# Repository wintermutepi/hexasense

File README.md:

HexaSense
=========

This is a prototyping project for a room heating controller based on the
HexaBus architecture. Nothing spectacular to see here - this is just a
playground.

### License

The UART code is written by Peter Fleury. Everything else: BSD 2-clause
license as below:

Copyright (c) 2012, Mathias Dalheimer
All rights reserved.

Redistribution and use in source and binary forms, with or without
modification, are permitted provided that the following conditions are
met:

* Redistributions of source code must retain the above copyright notice, 
this list of conditions and the following disclaimer.

* Redistributions in binary form must reproduce the above copyright
notice, this list of conditions and the following disclaimer in the
documentation and/or other materials provided with the distribution.

THIS SOFTWARE IS PROVIDED BY THE COPYRIGHT HOLDERS AND CONTRIBUTORS "AS
IS" AND ANY EXPRESS OR IMPLIED WARRANTIES, INCLUDING, BUT NOT LIMITED
TO, THE IMPLIED WARRANTIES OF MERCHANTABILITY AND FITNESS FOR A
PARTICULAR PURPOSE ARE DISCLAIMED. IN NO EVENT SHALL THE COPYRIGHT
HOLDER OR CONTRIBUTORS BE LIABLE FOR ANY DIRECT, INDIRECT, INCIDENTAL,
SPECIAL, EXEMPLARY, OR CONSEQUENTIAL DAMAGES (INCLUDING, BUT NOT
LIMITED TO, PROCUREMENT OF SUBSTITUTE GOODS OR SERVICES; LOSS
OF USE, DATA, OR PROFITS; OR BUSINESS INTERRUPTION) HOWEVER
CAUSED AND ON ANY THEORY OF LIABILITY, WHETHER IN CONTRACT,
STRICT LIABILITY, OR TORT (INCLUDING NEGLIGENCE OR OTHERWISE)
ARISING IN ANY WAY OUT OF THE USE OF THIS SOFTWARE, EVEN IF ADVISED OF
THE POSSIBILITY OF SUCH DAMAGE.

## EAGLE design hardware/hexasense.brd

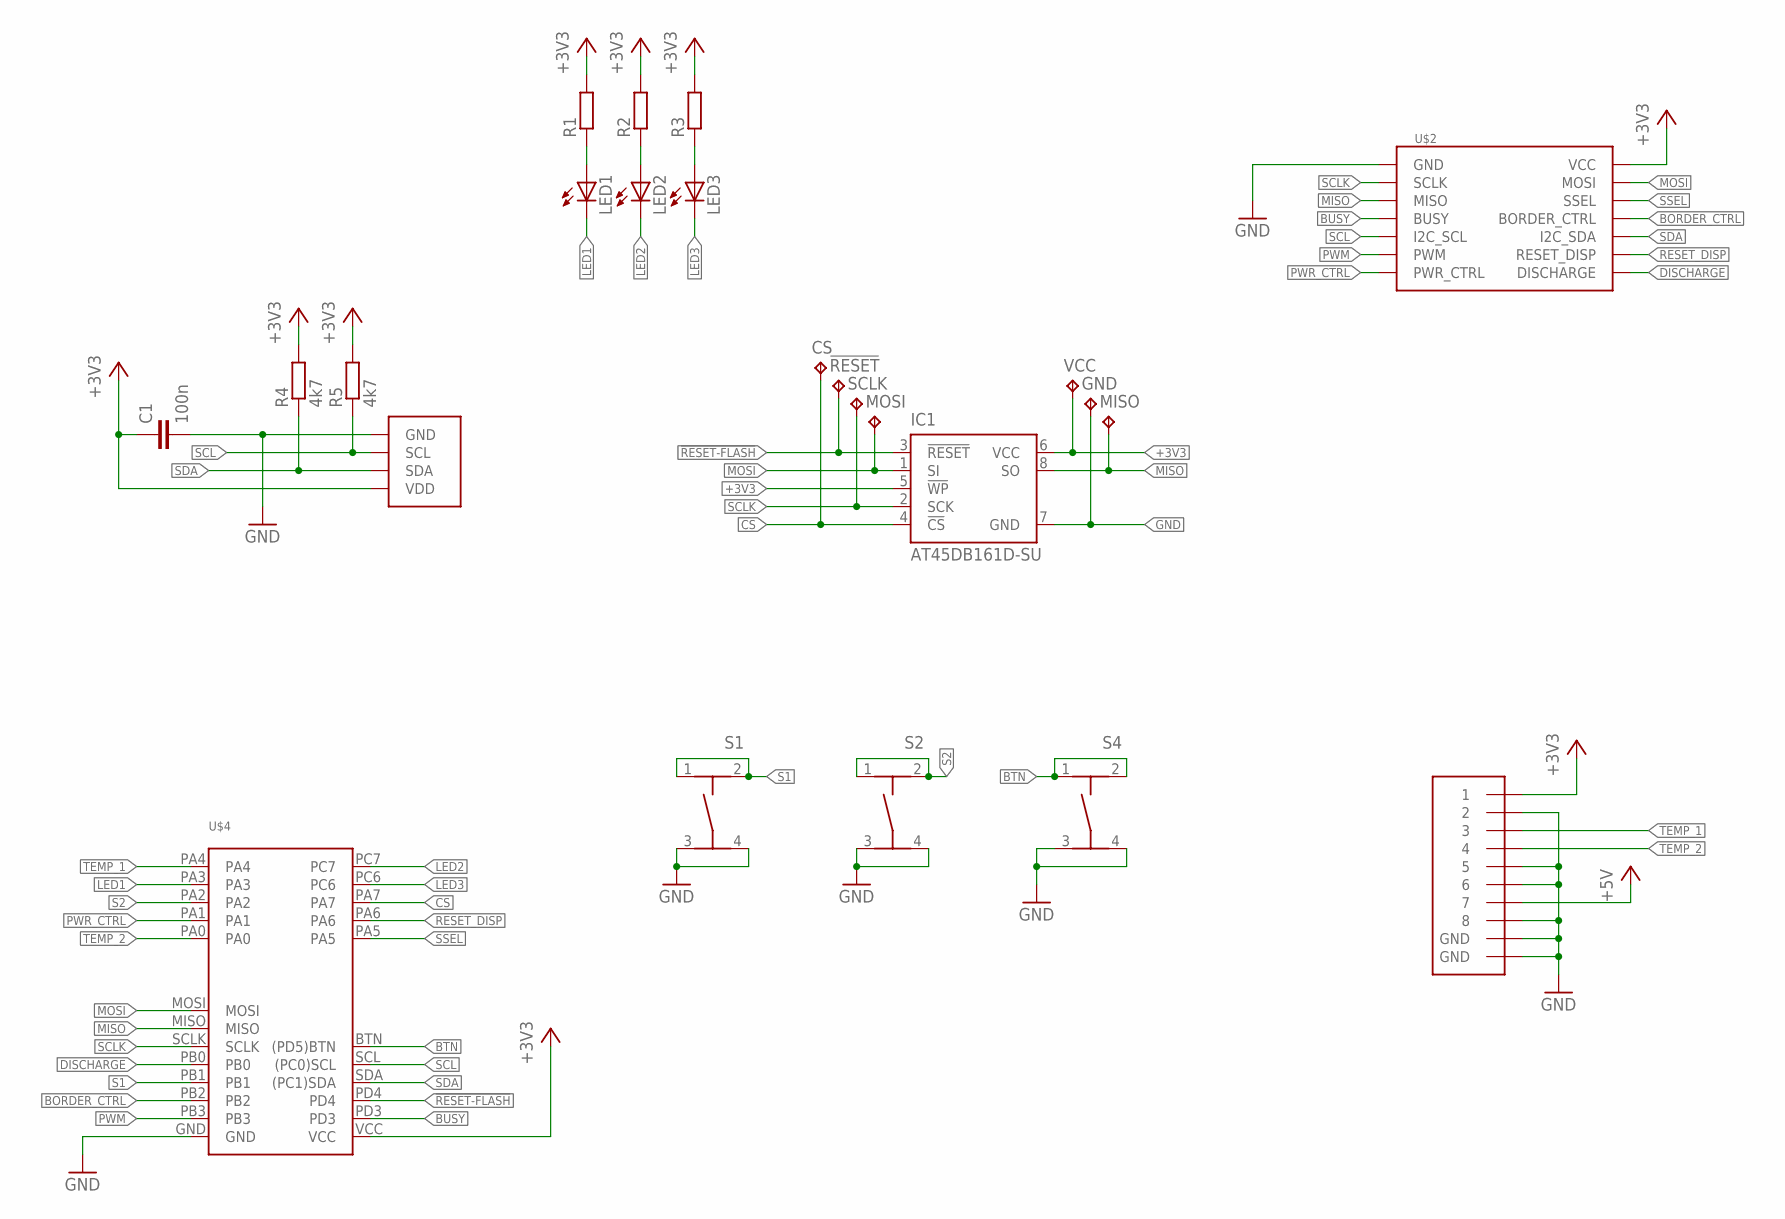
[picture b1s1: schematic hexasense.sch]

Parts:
!RESET: TPB1,27; B1,27
C1: 100n; C0805
CS: TPB1,27; B1,27
GND: TPB1,27; B1,27
IC1: AT45DB161D-SU; 8S2
LED1, LED2, LED3: LED3MM
MISO: TPB1,27; B1,27
MOSI: TPB1,27; B1,27
R1, R2, R3: R-EU_R0805; R0805
R4, R5: 4k7; R0805
S1, S2, S4: TASTER-9314_SMD
SCLK: TPB1,27; B1,27
U$1: MEBP8-8G; RJ45-REICHELT
U$2: EPAPER
U$4: HEXABUS
U$7: HYT271
VCC: TPB1,27; B1,27

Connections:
!RESET-FLASH: !RESET.TP, IC1.3 (!RESET), U$4.PD4
+3V3: C1.1, IC1.5 (!WP), IC1.6 (VCC), R1.2, R2.2, R3.2, R4.2, R5.2, U$1.1, U$2.P2 (VCC), U$4.VCC, U$7.VDD, VCC.TP
+5V: U$1.7
BORDER_CTRL: U$2.P8 (BORDER_CTRL), U$4.PB2
BTN: S4.1, S4.2, U$4.BTN ((PD5)BTN)
BUSY: U$2.P7 (BUSY), U$4.PD3
CS: CS.TP, IC1.4 (!CS), U$4.PA7
DISCHARGE: U$2.P14 (DISCHARGE), U$4.PB0
GND: C1.2, GND.TP, IC1.7 (GND), S1.3, S1.4, S2.3, S2.4, S4.3, S4.4, U$1.2, U$1.5, U$1.6, U$1.8, U$1.GND@1 (GND), U$1.GND@2 (GND), U$2.P1 (GND), U$4.GND, U$7.GND
LED1: LED1.K (C), U$4.PA3
LED2: LED2.K (C), U$4.PC7
LED3: LED3.K (C), U$4.PC6
MISO: IC1.8 (SO), MISO.TP, U$2.P5 (MISO), U$4.MISO
MOSI: IC1.1 (SI), MOSI.TP, U$2.P4 (MOSI), U$4.MOSI
unnamed: LED3.A, R3.1
unnamed: LED2.A, R2.1
unnamed: LED1.A, R1.1
PWM: U$2.P11 (PWM), U$4.PB3
PWR_CTRL: U$2.P13 (PWR_CTRL), U$4.PA1
RESET_DISP: U$2.P12 (RESET_DISP), U$4.PA6
S1: S1.1, S1.2, U$4.PB1
S2: S2.1, S2.2, U$4.PA2
SCL: R5.1, U$2.P9 (I2C_SCL), U$4.SCL ((PC0)SCL), U$7.SCL
SCLK: IC1.2 (SCK), SCLK.TP, U$2.P3 (SCLK), U$4.SCLK
SDA: R4.1, U$2.P10 (I2C_SDA), U$4.SDA ((PC1)SDA), U$7.SDA
SSEL: U$2.P6 (SSEL), U$4.PA5
TEMP_1: U$1.3, U$4.PA4
TEMP_2: U$1.4, U$4.PA0

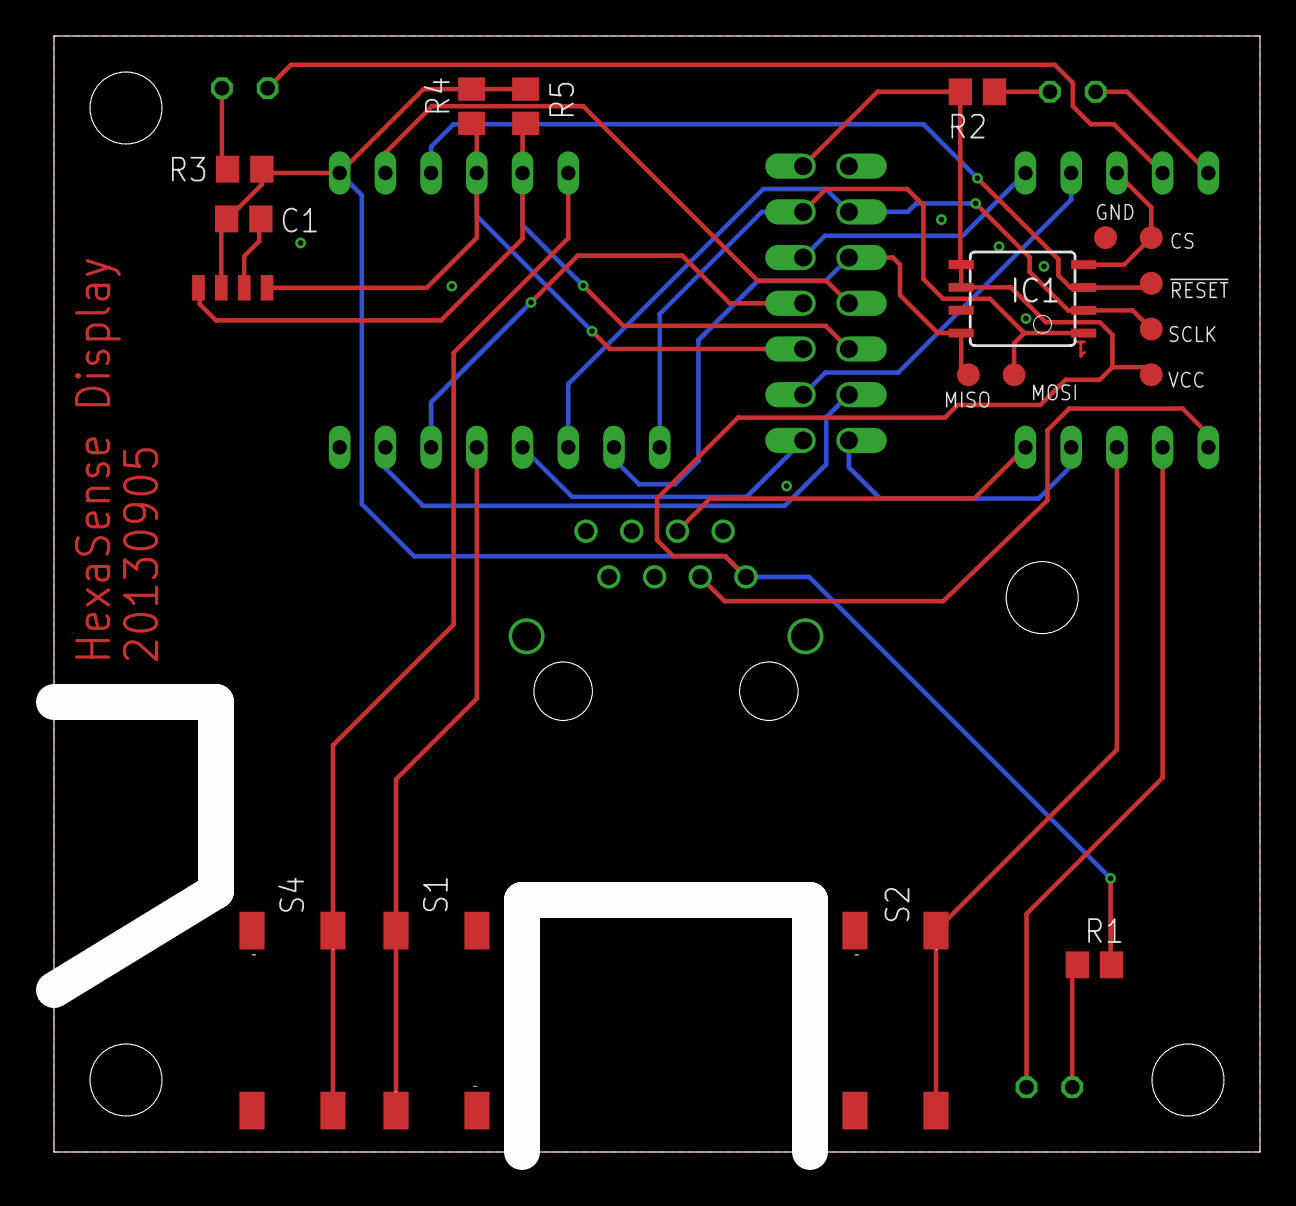
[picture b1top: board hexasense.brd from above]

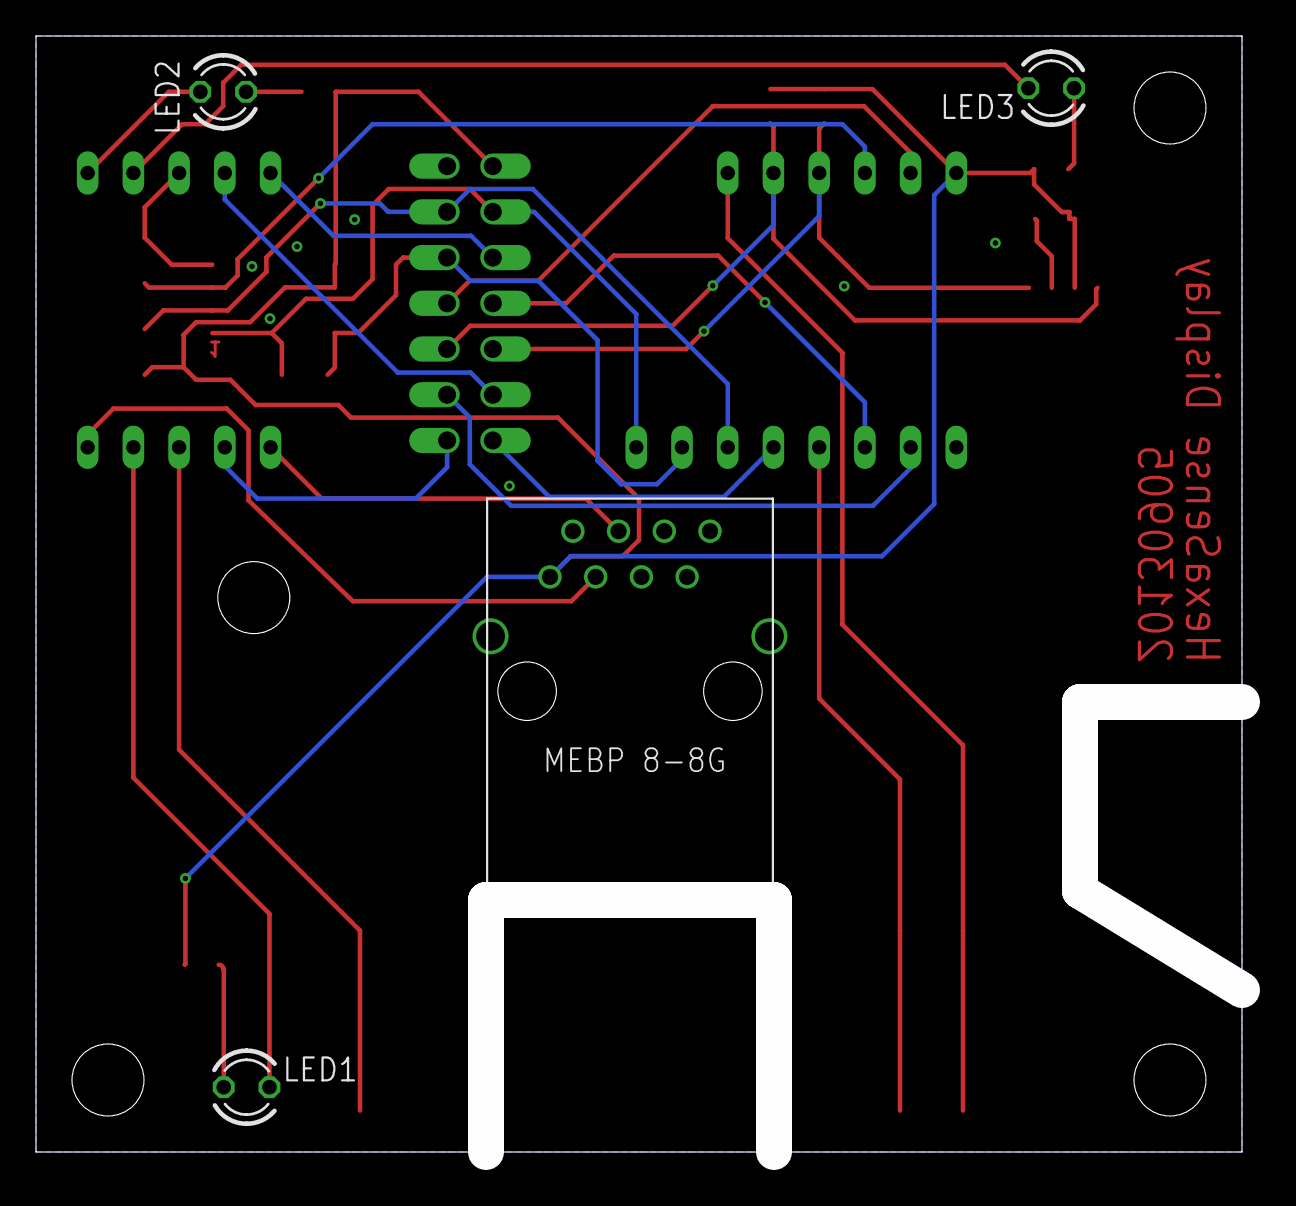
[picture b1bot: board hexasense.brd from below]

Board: 2 copper layers, 66.0 x 61.0 mm, 24 parts (5 on the bottom side), 27 nets.

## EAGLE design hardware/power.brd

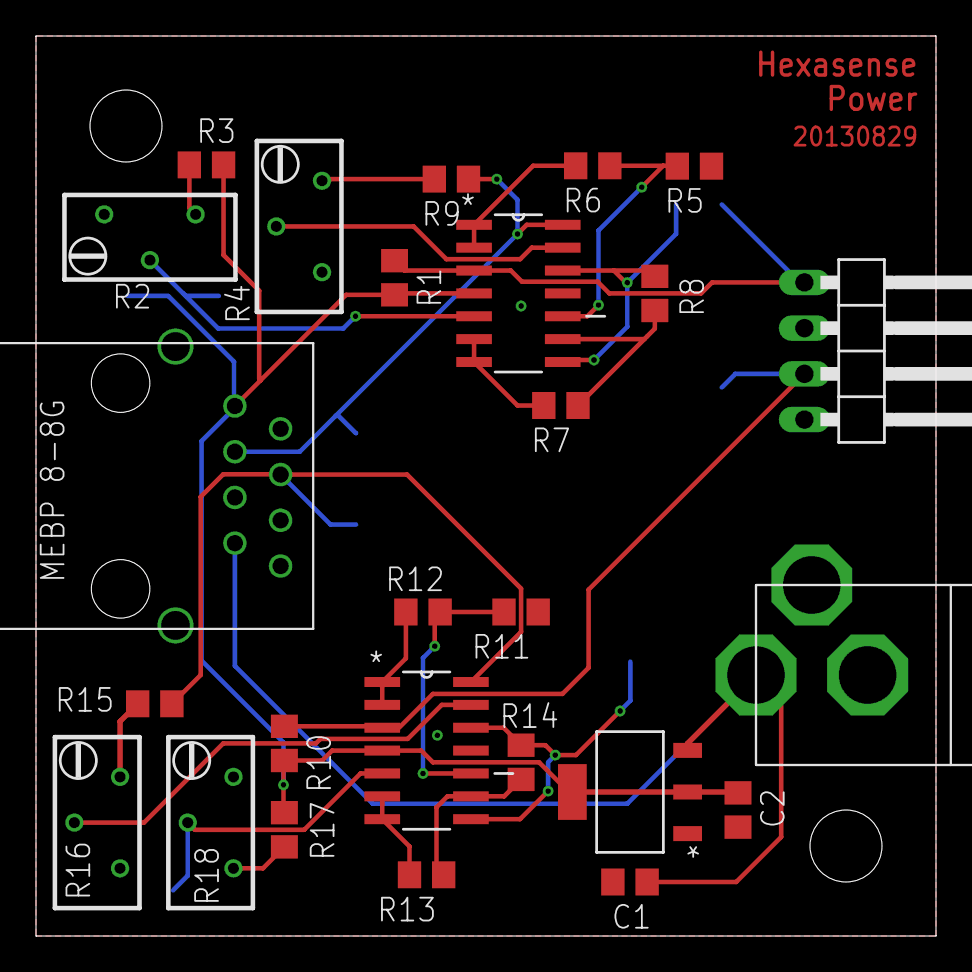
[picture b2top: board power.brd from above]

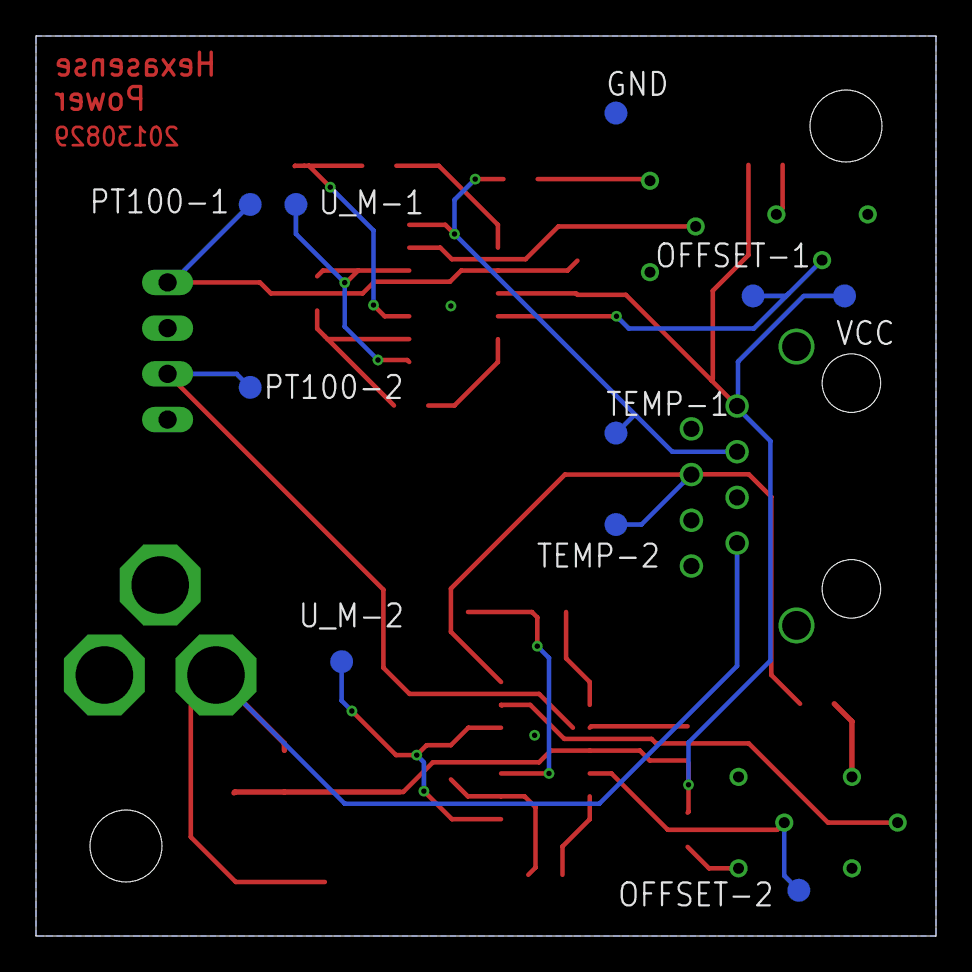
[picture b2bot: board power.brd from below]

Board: 2 copper layers, 50.0 x 50.0 mm, 36 parts (10 on the bottom side), 25 nets.

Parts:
C1, C2: 10uF; C0805
GND: TPB1,27; B1,27
JP2: 1X04/90
OFFSET-1, OFFSET-2: TPB1,27; B1,27
PT100-1, PT100-2: TPB1,27; B1,27
R1, R10: 1k; R0805
R2, R18: 10k; RTRIMT93YB
R3, R17: 100k; R0805
R4, R16: 20k; RTRIMT93YB
R5, R6, R7, R8, R11, R12, R13, R14: 470k; R0805
R9, R15: 47k; R0805
TEMP-1, TEMP-2: TPB1,27; B1,27
U1, U2: LM324D; SOIC127P600X175-14N
U3: LM1117MP-3.3; SOT230P696X180-4N
U$1: MEBP8-8G; RJ45-REICHELT
U$2: HOHLBUCHSE
U_M-1, U_M-2: TPB1,27; B1,27
VCC: TPB1,27; B1,27

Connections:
+3V3: C2.1, R1.2, R3.2, R10.2, R17.2, U1.4, U2.4, U3.2, U3.4, U$1.1, VCC.TP
+5V: C1.1, U3.3, U$1.7, U$2.I
GND: C1.2, C2.2, GND.TP, JP2.2, JP2.4, R2.3, R4.1, R5.1, R11.1, R16.1, R18.3, U1.11, U2.11, U3.1, U$1.2, U$1.5, U$1.6, U$1.8, U$1.GND@1, U$1.GND@2, U$2.O
unnamed: R4.2, U1.13
unnamed: R5.2, R6.1, U1.10
unnamed: R2.1, R3.1
unnamed: R15.2, R16.3
unnamed: R6.2, U1.1, U1.2
unnamed: R16.2, U2.13
unnamed: R7.2, U1.6, U1.7
unnamed: R7.1, R8.1, U1.9
unnamed: R11.2, R12.1, U2.10
unnamed: R12.2, U2.1, U2.2
unnamed: R4.3, R9.2
unnamed: R13.2, U2.6, U2.7
unnamed: R13.1, R14.1, U2.9
unnamed: R17.1, R18.1
OFFSET_1: OFFSET-1.TP, R2.2, U1.5
OFFSET_2: OFFSET-2.TP, R18.2, U2.5
PT100_1: JP2.1, PT100-1.TP, R1.1, U1.3
PT100_2: JP2.3, PT100-2.TP, R10.1, U2.3
TEMP_1: R9.1, TEMP-1.TP, U1.14, U$1.3
TEMP_2: R15.1, TEMP-2.TP, U2.14, U$1.4
U_M_1: R8.2, U1.8, U1.12, U_M-1.TP
U_M_2: R14.2, U2.8, U2.12, U_M-2.TP

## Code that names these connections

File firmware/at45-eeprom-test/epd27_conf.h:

#ifndef EPD27_CONF_H
#define EPD27_CONF_H 1

/**
 * Definition for the 2"7 display
 */

// output
#define EPD_PIN_EPD_CS PA5
#define EPD_PORT_EPD_CS PORTA
#define EPD_DDR_EPD_CS DDRA

// output
#define EPD_PIN_PANEL_ON PA1
#define EPD_PORT_PANEL_ON PORTA
#define EPD_DDR_PANEL_ON DDRA

// BORDER 
#define EPD_PIN_BORDER PB2
#define EPD_PORT_BORDER PORTB
#define EPD_DDR_BORDER DDRB

// output
#define EPD_PIN_DISCHARGE PB0
#define EPD_PORT_DISCHARGE PORTB
#define EPD_DDR_DISCHARGE DDRB

// output
#define EPD_PIN_PWM PB3
#define EPD_PORT_PWM PORTB
#define EPD_DDR_PWM DDRB

// output
#define EPD_PIN_RESET PA6
#define EPD_PORT_RESET PORTA
#define EPD_DDR_RESET DDRA

//input
#define EPD_PIN_BUSY PD3
#define EPD_PORT_BUSY PORTD
#define EPD_INPUT_PORT_BUSY PIND
#define EPD_DDR_BUSY DDRD

#define STAGE_TIME 630
#define LINES_PER_DISPLAY 176
#define DOTS_PER_LINE 264
#define BYTES_PER_LINE 264/8
#define BYTES_PER_SCAN 176/4
#define FILLER true



#endif /* EPD27_CONF_H */

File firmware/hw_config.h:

#ifndef HW_CONFIG_H
#define HW_CONFIG_H 1

/**
 * Connection of the DHT22 sensor.
 */
#define DHT22_PIN    PD3
#define DHT22_PORT   PORTD
#define DHT22_DDR    DDRD
#define DHT22_PINC   PIND


/**
 * Connection of the first button: PA1
 */
#define BTN0_DDR	DDRA
#define BTN0_PORT	PORTA
#define BTN0_PIN	PA1
#define BTN0_IN		PINA

/**
 * Connection of the second button: PA2
 */
#define BTN1_DDR	DDRA
#define BTN1_PORT	PORTA
#define BTN1_PIN	PA2
#define BTN1_IN		PINA

/**
 * Connection of the third button: PA3
 */
#define BTN2_DDR	DDRA
#define BTN2_PORT	PORTA
#define BTN2_PIN	PA3
#define BTN2_IN		PINA






#endif /* HW_CONFIG_H */

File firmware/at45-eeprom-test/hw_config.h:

#ifndef HW_CONFIG_H
#define HW_CONFIG_H 1

/**
<<<<<<< HEAD
 * Connection of the first button: PA1
=======
 * Connection of the first button
>>>>>>> dk-bringup
 */
#define BTN0_DDR	DDRB
#define BTN0_PORT	PORTB
#define BTN0_PIN	PB1
#define BTN0_IN		PINB

/**
<<<<<<< HEAD
 * Connection of the second button: PA2
=======
 * Connection of the second button
>>>>>>> dk-bringup
 */
#define BTN1_DDR	DDRA
#define BTN1_PORT	PORTA
#define BTN1_PIN	PA2
#define BTN1_IN		PINA

/**
<<<<<<< HEAD
=======
 * Connection of the third button (hxb-pairing button)
 */
#define BTN2_DDR	DDRD
#define BTN2_PORT	PORTD
#define BTN2_PIN	PD5
#define BTN2_IN		PIND

/**
>>>>>>> dk-bringup
 * I2C error codes.
 */
#define I2C_ERROR 1
#define I2C_SUCCESS 0

/**
 * PCA9532 I2C bus definitions
 */
#define PCA9532_ADDR  0xC0
#define PCA9532_FULL 0x55
#define PCA9532_OFF 0x00

/**
 * HYT271 I2C bus definitions
 */
#define HYT271_ADDR (0x28 << 1)
#define HYT271_CONV_DELAY 6
#define HYT271_BUFFER_LEN 4

/**
 * analog temperature sensors and respective adc channel
 */
#define ANALOG_TEMPERATURE_0 0
#define ANALOG_TEMPERATURE_1 4

#endif /* HW_CONFIG_H */

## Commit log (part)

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2012-12-18 redone humidity sensor package
2012-12-18 rearranged schematic
2012-12-18 further rearrangement of LEDs, some routing
2013-01-03 implemented button abstraction.
2013-01-03 minor updates on the comments, code cleanup
2013-01-03 added readme, formatting.
2013-01-04 added LED driver chip
2013-01-04 added push buttons and completed schematic for LED driver
2013-01-07 added led driver
2013-01-07 switched to Autodesk Inventor for enclosure design
2013-01-07 abandoning.
2013-01-07 new design, several components (used derive)
2013-01-07 might work.
2013-01-09 redesign completed (except for screw head)
2013-01-10 changed screw to self-tapping DIN 7981
2013-01-10 first release candidate
2013-01-11 added milling
2013-01-11 removed +12V from RJ45 connector
2013-01-11 new position for the push buttons. therefore a lot of rearanging
2013-01-11 minor tweaks, 3mm thickness for all walls.
2013-01-11 moved to power_board subdirectory
2013-01-11 done the routing
2013-01-11 first components of sense enclosure
2013-01-11 update of STL files.
2013-01-14 changed placement of buttons and leds. Did the necessary rerouting. Added a version number.
2013-01-14 schraubendim. korrigiert, ausschnitte vergroessert
2013-01-14 implemented a simple PCB model.
2013-01-14 added pcb model
2013-01-15 changed drill size
2013-01-15 replaced some parts. rearranged parts
2013-01-16 completed rerouting
2013-01-16 updated version number
2013-01-16 Changed outer distance to 6mm. Fixes #2
2013-01-18 added capacitor for volage regulator. Fixing #9
2013-01-18 basic outline of base component defined.
2013-01-21 fixes #13
2013-01-21 incresed drill size for humidity sensor. Fixes #11
2013-01-21 cleanup at RJ45 connector, finalized LM324
2013-01-21 duplicated measuring aplifier
2013-01-21 preliminary placement of new parts. ripup *
2013-01-22 corrected some wiring errors around the measuring amp
2013-01-22 added 2nd temperature signal to schematic
2013-01-22 basic routines are working on hardware prototype
2013-01-22 routing of 2nd temperature signal and pullups
2013-01-23 added led driver boilerplate code, adjusted hardware config accordingly.
2013-01-23 added empty routine for conversion from adc value to temperature
2013-01-23 code for temperature conversion - not yet testet; include .swp files in gitignore
2013-01-24 code for temperature conversion now compiling
2013-01-24 debug oputput
2013-01-24 cast adc value to float
2013-01-24 corrected upper limit
2013-01-24 set constants as float
2013-01-24 changed adc reference to internal 1.1V
2013-01-24 changed LED resistors to more fitting values
2013-01-28 played with i2c led driver.
2013-01-29 changed upper adc limit, since adc reference has been changed
2013-01-29 first prototype.
2013-01-29 fixed distance bug.
2013-01-29 test routine for gedoens
2013-01-30 output in one line, separated by semicolon
2013-01-30 holes for wall-mounting
2013-01-30 repositioned hexabus module. fixes #23
2013-01-30 added grills.
2013-01-30 schrauben hinzugefuegt
2013-01-31 ripup *
2013-01-31 added HYT271 humidity sensor
2013-01-31 resolved inconsistency between board and schematic
2013-01-31 horst
2013-01-31 loch fuer kabeldurchfuehrung hinzugefuegt
2013-01-31 lochdurchmesser vergroessert
2013-01-31 updated stl export files.
2013-01-31 changed VDD for LEDs to +5V
2013-01-31 changed LED from 0805 to 5mm THT
2013-02-01 changed pin assignment of RJ45 connector
2013-02-01 frontplatte for cnc lasercutting
2013-02-01 flanke pushbutton verlaengert
2013-02-01 led placement
2013-02-01 removed ground plane from half the PCB to avoid heating the sensor(s)
2013-02-01 increased size of grill rips to prevent slicing fuckups.
2013-02-04 added cleaned frontplatte
2013-02-04 distributed LEDs evenly
2013-02-04 optimized position of reset button
2013-02-04 cleaned up position of led resistors and started routing
2013-02-04 some of the sensors were on the wrong side of the PCB
2013-02-04 abstraktion des i2c-busses, gruppierung der leds noch unklar (see issue #27)
2013-02-04 testprogramm vollstaendig, closes #19
2013-02-05 routing...
2013-02-05 more routing...
2013-02-05 finished routing
2013-02-05 passing the DRC
2013-02-05 added missing wire
2013-02-05 added GND around PWM lines leading to LEDs
2013-02-05 updated RJ45 connector to new pin assignment
2013-02-05 added driver for hygrosens HYT271 humidity sensor
2013-02-05 set the distance case - PCB as defined in #2
2013-02-05 added dewpoint calculation
2013-02-06 introduced supersampling - currently untested! fixes #29, fixes #30
2013-02-06 enabled -Werror compiler flag, fixed errors that have been warnings before.
2013-02-06 dos2unix
2013-02-06 implemented proper DHT22 error reporting.
2013-02-06 stuff
2013-02-06 removed \r\n
2013-02-06 changed something
2013-02-06 bend wires in 45 deg angle
2013-02-06 removed unneeded GND polygon
2013-02-06 UNTESTED code: two modi for post-production evaluation and stresstest via #define
2013-02-07 added 100nF capacitors to humidity sensor and LED chip
2013-02-07 added pin1 info for led chip
2013-02-07 use all pins of the buttons
2013-02-07 Bemaßungen
2013-02-07 redid some routing
2013-02-07 changed even more routing
2013-02-07 preliminary placement and routing
2013-02-07 now passing the DRC
2013-02-07 arranged position of testpads to multiples of 2.54
2013-02-07 cleaned up placement print
2013-02-07 changed testpads to THT
2013-02-07 moved placement print
2013-02-18 changed circuitry for C1 and voltage regulator
2013-02-21 corrected power supply for LEDs.
2013-02-25 removed a newline in the debug output
2013-02-25 corrected placement print for LEDs 8 and 9
2013-02-26 up-to-date export of STLs (already rotated)
2013-02-28 changed cooling ribs to cooling holes
2013-03-05 rev2 dimensions
2013-03-06 completed case rev2
2013-03-06 cutouts for components added.
2013-03-07 removed DHT22 code
2013-03-07 added 2nd ADC channel
2013-03-08 kleinere korrekturen - anpassung an platine
2013-03-11 added calibration analysis
2013-03-11 renamed data file
2013-03-13 added new dataset
2013-03-14 added measurements for red leds on
2013-04-15 separate subdirectory for AT45 test, created boilerplate firmware
2013-04-15 removed unnecessary TWI files.
2013-04-16 simple buffer read/write implemented
2013-04-17 refactored at45 test code to be in a separate file.
2013-04-17 added EAGLE libraries
2013-04-17 changed display board for use of epaper
2013-04-17 added flash chip
2013-04-17 placed flash chip on pcb
2013-04-25 basic driver working - clear operation tested and functional.
2013-04-25 cat picture now being displayed.
2013-05-03 foundation of flash upload tool.
2013-05-03 now using a real footprint for the epaper display. work in progress
2013-05-08 added LEDs
2013-05-08 cleaning up the schematic
2013-05-15 added missing wires
2013-06-14 added reset and SCLK line for flash chip
2013-06-14 added testpads to schematic
2013-06-17 testpads and placement print
2013-06-19 several minor changes
2013-06-28 final changes
2013-07-08 ruby host software: can erase at45 via buspirate
2013-07-08 removed malfunctioning c software
2013-07-09 added ruby-buspirate as a git submodule
2013-07-09 changed code for running on atmega1284
2013-07-10 changed definitions for EPD, working on target hardware
2013-07-10 added code for temperature sensor from led_module_firmware
2013-07-10 makefile and main.c for temperature sensor
2013-07-10 added code for dew point calculation
2013-07-11 added dew_point.c and .h
2013-07-11 added adc code
2013-07-11 call read_analog_sensors
2013-07-11 to get proper measurements, we should init the adc...
2013-07-11 added buttons - caution this get stuck in an while(1) loop!
2013-07-11 buttons nneed init too
2013-07-11 button loop now terminats after pressing a button
2013-07-11 removal of old code
2013-07-11 power off epaper display after use
2013-07-11 how to calibrate the analog sensors
2013-07-12 more instructions in the output, include testing of the pairing button
2013-07-12 give the buttons easier understandable names
2013-07-12 implemented basic commands and testsuite, all tests pass
2013-07-16 stability of testsuite greatly improved.
2013-07-16 implemented long-running tests.
2013-07-17 changed upload_page call to reflect new function name (in all places)
2013-07-17 resolved another merge conflict.
2013-07-23 treat eagle files as binary
2013-07-23 connected BORDER_CTRL
2013-07-23 changed 6mm drill hole for display mount to 10x10mm milling
2013-07-24 rev B of epd has border_ctrl connected
2013-07-24 converter should(TM) work, not fully tested b/c of missing hardware
2013-07-24 simple image generator for test purposes, rendered lots of images
2013-07-29 cleanup of converter code, small changes to flash format
2013-07-29 fixed wrong pagesize - 264 it is.
2013-07-29 denoisified verbose console output
2013-07-30 adjusted page erase mechanism - works if individual pages are erased before programming (-s cmd line parameter)
2013-07-31 at45 bringup test: comm. w/ AT45 is working, data not yet read out.
2013-07-31 removed all pics
2013-07-31 added pics folder and readme
2013-07-31 ignore all pngs in the pics folder
2013-08-01 read correct table in datasheet, appears to be working now (bonus feature: correct page size!)
2013-08-05 implemented readout of temp-hum loopup table
2013-08-05 added default pattern to all unused LUT locations.
2013-08-06 fixed wrong wiring at voltage regulator
2013-08-07 incorporated stress test in the current firmware
2013-08-09 working version of picture display, needs cleanup and refactoring
2013-08-13 implemented testsuite, at45 service routines, epd from at45 functions
2013-08-13 refactored value ranges.
2013-08-22 moved S4 away from hole
2013-08-22 increased milling to allow for more tolerance
2013-08-22 added sensor board v2 enclosure project
2013-08-28 changed milling to accommodate case
2013-08-29 upper and lower enclosure complete w/o button feature.
2013-08-29 changed testpoints to SMD pads
2013-08-29 minor touchups on power board
2013-08-29 minor touchups on sense board
2013-09-02 updated to newest version of epd footprint
2013-09-03 added preview of new enclosure
2013-09-05 added I2C pullups
2013-09-05 routing of i2c pullups
2013-09-09 allow partial flash write
2013-09-09 implement basic image particle generator and compositor
2013-09-10 add logic for recommendation generation
2013-09-16 minor adjustments
2013-09-18 corrected measurements
2013-09-19 don't draw a border around screens
2013-10-01 adjusted the position of the epaper display slightly.
2013-10-01 pushbuttons added
2013-10-01 add special screen generation
2013-10-01 rotate generated images to not be upside down on the hexasense display
2013-10-01 innenloch von 3,3mm auf 3,5mm erweitert
2013-10-07 documentation of calibration rig
2013-10-08 added U_M to switch
2013-10-08 Unterschale: Führungen für die Oberschale
2013-10-08 Displayausschnitt verschoben
2013-10-08 innenloch knopf vergroessert
2013-10-08 display-boss entfernt
2013-10-08 STLs fuer staender hinzugefuegt
2013-10-11 minor details
2013-10-15 final tweaks.
2013-10-15 added two additional bosses.
2013-10-16 senkkopfschrauben
2013-10-16 added paper reference
2013-10-16 added 3d printer job submission files to gitignore
2013-10-18 add particle images for the generators
2013-10-30 kernlochdurchmesser angepasst, boss entfernt, loecher abgedeckt
2013-10-30 radien etc. korrigiert
2013-10-30 neuer export, diesmal mit korrekten Einheiten exportiert
2013-11-13 updated good value zone, prepared DRY pics
2013-11-13 add picture "increase humidity"
2013-11-14 fixes #39, included stl export of gehaeuse
2013-11-18 fixed 2mm gap caused by elevated display connector
2013-11-19 update "increse humidity" picture
2013-12-02 add --retry option to image uploader
2013-12-03 Documentation (Installations-/Bedienungsanleitung)
    This will contain the documentation, especially sketches, images, photos etc. for hexasense
2013-12-03 added sketches of hexasense and hexabus base station for documentation purposes - see wiki pages
